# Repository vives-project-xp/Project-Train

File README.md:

# Project-Train 

## Doel project
Ons project zal worden gebruikt in een escape room. 
De bedoeling is dat er allerlei dingen gebeuren in de kamer om de sperlers
hun aandacht te trekken. Onze trein zal daar bij horen.
De trein zal in een tijd van 10sec naar de overkant van de kamer 
moeten rijden. Dit zal allemaal automatisch gebeuren. 
Ook zal er een ledstip die aan de muur gangt de trein moeten volgen.

### H-Brug
Aan de hand van de H-Brug zullen we de trein aumtomatisch doen rijden. De snelheid
en de richting waarin de trein rijdt kan worden bepaald. De trein wordt geleverd met 
een draai knop om de snelheid en richting te bepalen de H-Brug zal deze dan vervangen.
Doordat we onze componenten te laat binnen kregen en een snelle oplossing moesten zoeken hiervoor
hebben we een andere component gebruikt. 

### Ledstrip
De led strip zal de trein moeten volgen zodat de aandacht
van de spelers naar de trein gaat. Dit zal gebeuren aan de hand van 
sensors die onder de trein staan. Zo kunnen we perfect weten waar de trein zich
bevint en kunnen we de ledstip programeren. We maken gebruik van een infrarood LED en een sensor. Wanneer er een object, de trein in ons geval, over deze LED en sensor rijdt zal de sensor een digitale '1' uitsturen.
In totaal hebben we 8 LEDs en sensoren, hierdoor krijgen we 8 nulletjes en eentjes binnen. Wanneer er dus een reeks van eentjes binnenkomt weten we dat de trein zich daar bevindt. Doordat we weten waar de trein zich bevindt 
kunnen we zo de LEDs aansturen om te branden waar we een '1' binnenlezen en niet te branden waar we een '0' binnenlezen.

### De sensor 
De sensoren die zich onder de trein bevinden zullen uit een fototransistor en
een infrarood led bestaan. Wanneer de trein over de sensor rijdt zal
er door de weerkaatsing van het licht een signaal worden binnengelezen. Dit signaal
kunnen we dan gebruiken. Omdat we heel wat sensors hebben gaan we deze binnen 
lezen aan de hand van schuifregisters.

### Lichten in de trein
Dit is even op hold gezet omdat er balangrijkere dingen waren maar, de bedoeling was dat
er 2 koperen staven op het spoor kwamen te liggen die verbonden zijn met een DC-DC convertor.
Hierop komen 2 veren die vasthangen aan de laatste wagon die ervoor zorgt dat de schakeling in de 
wagon voeding krijgt. De staven lopen niet helemaal door, daarom zou er een condensator in de schakeling 
zitten die na het opladen en het verlaten van de koperen staven zorgt dat de schakeling nog spanning heeft voor derest van het traject.

### Video en presentatie
Voor ons project hebben we ook een video moeten maken. De link naar deze video kan je hier terugvinden:

https://vivesonline-my.sharepoint.com/personal/r0946707_student_vives_be/_layouts/15/onedrive.aspx?id=%2Fpersonal%2Fr0946707%5Fstudent%5Fvives%5Fbe%2FDocuments%2FProject%20Trein%2FProject%20Trein%2Emp4&parent=%2Fpersonal%2Fr0946707%5Fstudent%5Fvives%5Fbe%2FDocuments%2FProject%20Trein

Ook hebben we een presentatie moeten maken. De link naar die presentatie kan je ook hier terugvinden:

https://vivesonline-my.sharepoint.com/:p:/r/personal/r0946707_student_vives_be/_layouts/15/Doc.aspx?sourcedoc=%7B4A128648-7F8D-40A9-8AE3-8421E35680C3%7D&file=Project%20Trein.pptx&action=edit&mobileredirect=true

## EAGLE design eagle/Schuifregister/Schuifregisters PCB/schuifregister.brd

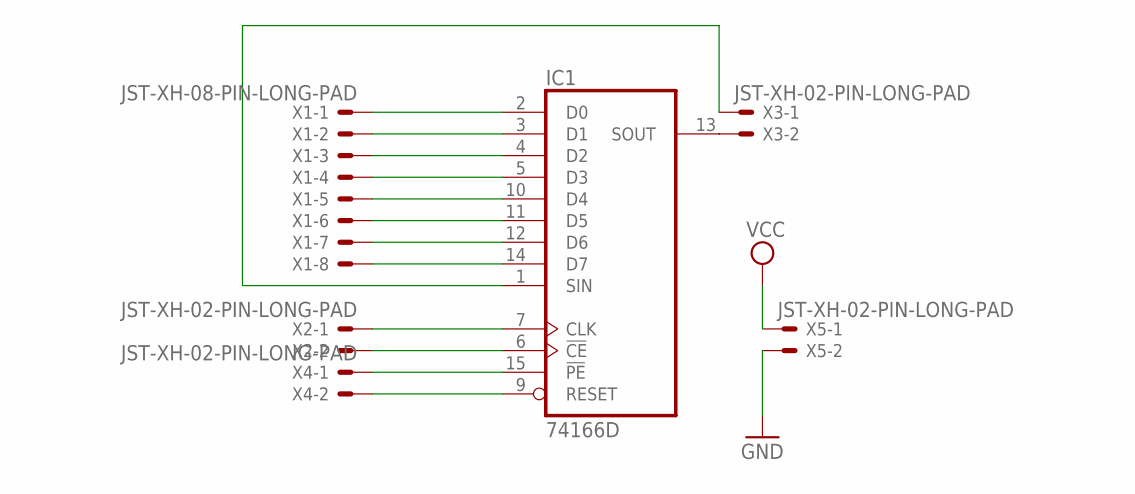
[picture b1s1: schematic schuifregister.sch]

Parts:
IC1: 74166D; SO16
X1: JST-XH-08-PIN-LONG-PAD; JST-XH-08-PACKAGE-LONG-PAD
X2, X3, X4, X5: JST-XH-02-PIN-LONG-PAD; JST-XH-02-PACKAGE-LONG-PAD

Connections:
GND: IC1.8 (GND), X5.2
unnamed: IC1.2 (D0), X1.1
unnamed: IC1.3 (D1), X1.2
unnamed: IC1.4 (D2), X1.3
unnamed: IC1.5 (D3), X1.4
unnamed: IC1.10 (D4), X1.5
unnamed: IC1.11 (D5), X1.6
unnamed: IC1.12 (D6), X1.7
unnamed: IC1.14 (D7), X1.8
unnamed: IC1.6 (!CE), X2.2
unnamed: IC1.7 (CLK), X2.1
unnamed: IC1.13 (SOUT), X3.2
unnamed: IC1.1 (SIN), X3.1
unnamed: IC1.9 (RESET), X4.2
unnamed: IC1.15 (!PE), X4.1
VCC: IC1.16 (VCC), X5.1

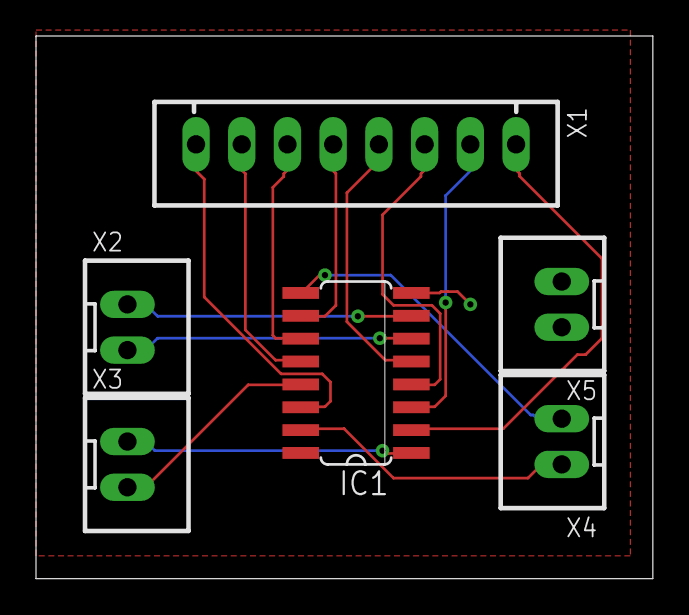
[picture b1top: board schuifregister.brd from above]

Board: 2 copper layers, 34.3 x 30.1 mm, 6 parts (0 on the bottom side), 16 nets.

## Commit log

2023-03-23 programma schuifregister gemaakt
2023-03-23 Create Project Train Code
2023-03-23 Update Project Train Code
2023-03-30 PCB infrarood gerber
2023-03-30 README.md
2023-03-30 readme gemaakt
2023-03-30 readme aangepast
2023-03-30 foto
2023-03-30 fototje
2023-03-30 foto van trein
2023-04-05 added gerber files of schuifregister PCB
2023-04-14 PCB lichten trein
2023-04-20 Added original PCB files to te repo
2023-04-27 schema sensor toegevoegd
2023-04-27 schema H-Brug
2023-04-27 nieuwe ReadMe gemaakt voor schekalingen
2023-04-27 schema's uitgelegd
2023-04-27 foto's verzet
2023-04-27 foto veranderd
2023-04-27 arduino
2023-04-27 aangepast
2023-04-27 verzwijzing toegevoegd
2023-04-27 foto aangepast
2023-04-27 foto bewerkt
2023-05-04 Update README.md
    updated
